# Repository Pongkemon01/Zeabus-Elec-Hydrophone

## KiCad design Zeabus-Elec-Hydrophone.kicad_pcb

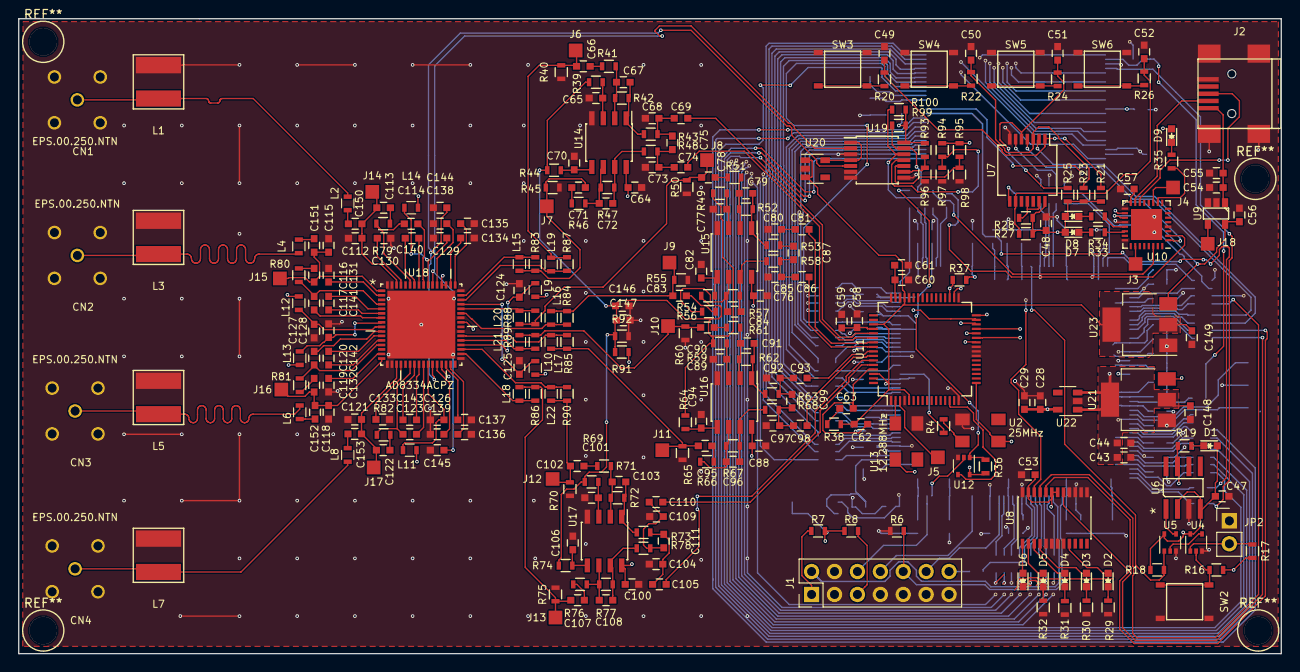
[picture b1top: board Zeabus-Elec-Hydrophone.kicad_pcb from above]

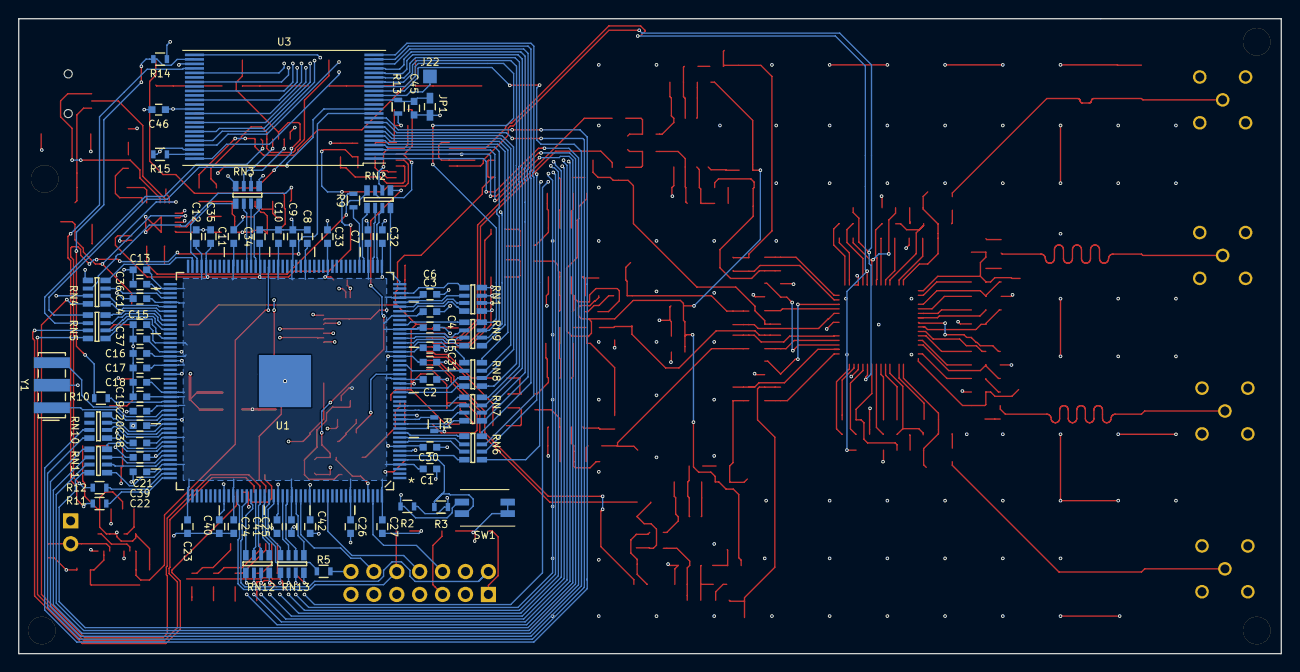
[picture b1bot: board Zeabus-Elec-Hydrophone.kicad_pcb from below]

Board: 4 copper layers, 140.0 x 70.4 mm, 352 parts (72 on the bottom side), 298 nets.

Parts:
C1, C2, C3, C4, C5, C6, C7, C8, C9, C10, C11, C12, C13, C14, C15, C16, C17, C18, C19, C20, C21, C22, C23, C24, C25, C26, C27, C30, C31, C32, C33, C34, C35, C36, C37, C38, C39, C40, C41, C42, C45, C46, C47, C48, C53, C55: 0.01uF; C_0603
C28, C29, C43, C44, C61, C146: 10uF; C_0603
C49, C50, C51, C52, C54, C56, C148, C149: 1uF; C_0603
C57, C58, C60, C64, C65, C70, C76, C77, C82, C88, C89, C94, C100, C101, C106, C114, C117, C120, C123, C124, C125, C126, C127, C128, C129, C130, C131, C132, C133, C134, C135, C136, C137, C138, C139, C140, C141, C142, C143, C150, C151, C152, C153: 0.1uF; C_0603
C59: 47uF; C_0603
C62: 390pF; C_0603
C63: 5600pF; C_0603
C66, C69, C71, C74, C78, C81, C83, C86, C90, C93, C95, C98, C102, C105, C107, C110: 22uF; C_0603
C67, C72, C79, C84, C91, C96, C103, C108: 300pF; C_0603
C68, C73, C80, C85, C92, C97, C104, C109, C144, C145: 1000pF; C_0603
C75, C87, C99, C111: 100pF; C_0603
C112, C115, C118, C121: 22pF; C_0603
C113, C116, C119, C122: 18000pF; C_0603
C147: 100uF; C_0603
CN1, CN2, CN3, CN4: EPS.00.250.NTN; EPS-00-250
D1, D2, D6: Yellow; LED_0603
D3, D8: Red; LED_0603
D4, D7: Blue; LED_0603
D5, D9: Green; LED_0603
J1: JTAG; Pin_Header_Straight_2x07_Pitch2.54mm
J2: USB_OTG; USB_Mini-B
J3, J4, J5, J6, J7, J8, J9, J10, J11, J12, J13, J14, J15, J16, J17, J18, J22: TEST_1P; 1Pin-TP
JP1: Write Protect; C_0603_HandSoldering
JP2: External Reset; Pin_Header_Straight_1x02_Pitch2.54mm
L1, L3, L5, L7: 15mH; L-SDR0503
L2, L4, L6, L8, L9, L10, L11, L12, L13, L14, L15, L16, L17, L18, L19, L20, L21, L22: 120nH; L_0603
R1, R2, R3, R7, R8, R13, R14, R15, R16, R17, R18, R21, R23, R25, R27, R28, R36, R37, R96, R97, R98, R99, R100: 10k; R_0603
R4, R5: 33; R_0603
R6: 47k; R_0603
R9, R10, R11, R12: 22; R_0603
R19, R29, R30, R31, R32, R33, R34, R35: 330; R_0603
R20, R22, R24, R26, R39, R44, R49, R54, R59, R64, R69, R74, R83, R84, R85, R86, R87, R88, R89, R90: 100; R_0603
R38: 560; R_0603
R40, R45, R50, R55, R60, R65, R70, R75: 49.9k; R_0603
R41, R46, R51, R56, R61, R66, R71, R76: 5.76k; R_0603
R42, R47, R52, R57, R62, R67, R72, R77: 4.99k; R_0603
R43, R48, R53, R58, R63, R68, R73, R78: 237; R_0603
R79, R80, R81, R82: 274; R_0603
R91: 806; R_0603
R92: 1k; R_0603
R93, R94, R95: 0; R_0603
RN1, RN2, RN3, RN4, RN5, RN6, RN7, RN8, RN9, RN10, RN11, RN12, RN13: EXBN8V-22; CRA06S
SW1: SW_DIP_x02; SW_DIP_x2_W5.08mm_Slide_Copal_CHS-A
SW2, SW3, SW4, SW5, SW6: PB; Button-EVQ
U1: ADSP-21489BSWZ-4B; ADSP-21489-177
U2: 25MHz; Oscillator-TCXO
U3: S29GL032N; TSOP-I-48_12x18.4mm_Pitch0.5mm
U4, U5, U12: 74LVC1G08; SOT-353
U6: ADM708SARZ; ADM708_R_8
U7: 74LVC14; SSOP-14_5.3x6.2mm_Pitch0.65mm
U8: 74AC11244; TSSOP-24_4.4x7.8mm_Pitch0.65mm
U9: NCP361SNT1G; TSOP-5
U10: FT232RQ; QFN-32-1EP_5x5mm_Pitch0.5mm
U11: AD1939WBSTZ; LQFP-64_10x10mm_Pitch0.5mm
U13: 12.288MHz; Oscillator-TCXO
U14, U15, U16, U17: AD8652ARZ; SOIC-8_3.9x4.9mm_Pitch1.27mm
U18: AD8334ACPZ; QFN50P900X900X100-65N
U19: MAX5387LAUD+T; TSSOP-14_4.4x5mm_Pitch0.65mm
U20: TLV73311PDBVT; SOT-23-5
U21, U23: LM1117-3.3; SOT-223-3Lead_TabPin2
U22: TLV73311PDVBT; SOT-23-5
Y1: CSTCC2M00G53-R0; Resonator_7.2x3mm

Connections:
+1V1: C1.1, C2.1, C3.1, C4.1, C5.1, C6.1, C7.1, C8.1, C9.1, C10.1, C11.1, C12.1, C13.1, C14.1, C15.1, C16.1, C17.1, C18.1, C19.1, C20.1, C21.1, C22.1, C23.1, C24.1, C25.1, C26.1, C27.1, C28.1, C29.1, U1.4, U1.23, U1.29, U1.34, U1.37, U1.41, U1.48, U1.62, U1.65, U1.68, U1.78, U1.85, U1.90, U1.93, U1.102, U1.105, U1.107, U1.113, U1.114, U1.116, U1.123, U1.129, U1.133, U1.143, U1.156, U1.169, U1.176, U22.5
+3.3VA: C62.1, C149.1, R38.2, U11.5, U11.45, U11.51, U11.62, U20.1, U20.3, U23.2
+3V3: C30.1, C31.1, C32.1, C33.1, C34.1, C35.1, C36.1, C37.1, C38.1, C39.1, C40.1, C41.1, C42.1, C43.1, C44.1, C46.1, C47.1, C48.1, C53.1, C148.1, D1.2, D7.2, D8.2, D9.2, R1.2, R7.2, R8.2, R13.1, R14.1, R16.1, R17.1, R18.1, R21.1, R23.1, R25.1, R27.1, R28.2, R36.1, R37.1, R93.1, R94.1, R95.1, R99.1, R100.1, SW1.1, SW1.2, U1.8, U1.28, U1.45, U1.57, U1.72, U1.84, U1.91, U1.104, U1.119, U1.126, U1.141, U1.153, U1.160, U2.VCC, U3.37, U4.5, U5.5, U6.2, U6.4, U7.14, U8.18, U8.19, U8.23, U11.17, U11.32, U12.5, U13.VCC, U19.14, U21.2, U22.1, U22.3
+5V: C56.1, C64.2, C76.2, C88.2, C100.2, L9.1, L10.1, L11.1, L12.1, L13.1, L14.1, R91.1, U9.5, U10.19, U14.8, U15.8, U16.8, U17.8, U18.29, U18.41, U18.51, U18.52, U21.3, U23.3
/ADC/ABCLK: RN3.1, U11.28
/ADC/ADC1LN: C74.2, U11.54
/ADC/ADC1LP: C69.2, U11.53
/ADC/ADC1RN: C86.2, U11.56
/ADC/ADC1RP: C81.2, U11.55
/ADC/ADC2LN: C98.2, U11.58
/ADC/ADC2LP: C93.2, U11.57
/ADC/ADC2RN: C110.2, U11.60
/ADC/ADC2RP: C105.2, U11.59
/ADC/ALRCLK: RN4.3, U11.29
/ADC/ASDATA1: RN4.1, U11.27
/ADC/ASDATA2: RN3.4, U11.26
/ADC/SPI_CLK: RN1.3, U11.34
/ADC/SPI_MISO: RN1.1, U11.31
/ADC/~AD1939_CS: R37.2, RN1.4, U11.35
/ADC/~AD1939_SOFT_RESET: R36.2, RN2.1, U12.1
/DSP-External_Port/DAI_P5_Z: RN4.8, U1.87
/DSP-External_Port/DAI_P6_Z: RN3.5, U1.86
/DSP-External_Port/DAI_P7_Z: RN3.8, U1.73
/DSP-External_Port/DAI_P8_Z: RN4.6, U1.94
/DSP-External_Port/DAI_P13_Z: RN3.7, U1.74
/DSP-External_Port/DAI_P14_Z: RN4.5, U1.95
/DSP-External_Port/DAI_P15_Z: RN5.5, U1.101
/DSP-External_Port/DAI_P16_Z: RN5.6, U1.99
/DSP-External_Port/DAI_P17_Z: RN5.7, U1.98
/DSP-External_Port/DAI_P18_Z: RN5.8, U1.97
/DSP-External_Port/DAI_P19_Z: RN3.6, U1.75
/DSP-External_Port/DAI_P20_Z: RN4.7, U1.92
/DSP-External_Port/DPI_P1_Z: RN1.8, U1.38
/DSP-External_Port/DPI_P2_Z: RN1.7, U1.39
/DSP-External_Port/DPI_P3_Z: RN1.6, U1.40
/DSP-External_Port/DPI_P5_Z: RN1.5, U1.42
/DSP-External_Port/DPI_P6_Z: RN2.8, U1.44
/DSP-External_Port/DPI_P7_Z: RN2.6, U1.47
/DSP-External_Port/DPI_P8_Z: RN2.7, U1.46
/DSP-External_Port/DPI_P9_Z: RN2.5, U1.49
/DSP-External_Port/DPI_P10_Z: R9.2, U1.50
/DSP-External_Port/LED1: RN3.2, U8.22
/DSP-External_Port/LED2: RN4.4, U8.21
/DSP-External_Port/LED3: RN5.4, U8.20
/DSP-External_Port/LED4: RN5.3, U8.17
/DSP-External_Port/PB1: RN5.2, U7.2
/DSP-External_Port/PB2: RN5.1, U7.4
/DSP-External_Port/PB3: RN3.3, U7.6
/DSP-External_Port/PB4: RN4.2, U7.8
/DSP-External_Port/SCL: R99.2, RN2.2, U19.13
/DSP-External_Port/SDA: R100.2, RN2.3, U19.12
/DSP-External_Port/SPI_MISO: RN1.2, U11.30
/DSP-External_Port/UART_RX: R9.1, U10.2
/DSP-External_Port/UART_TX: RN2.4, U10.30
/DSP-Memory/A0: RN6.1, U3.45
/DSP-Memory/A0_Z: RN6.8, U1.6
/DSP-Memory/A1: RN6.2, U3.25
/DSP-Memory/A1_Z: RN6.7, U1.9
/DSP-Memory/A2: RN6.3, U3.24
/DSP-Memory/A2_Z: RN6.6, U1.10
/DSP-Memory/A3: RN6.4, U3.23
/DSP-Memory/A3_Z: RN6.5, U1.11
/DSP-Memory/A4: RN7.1, U3.22
/DSP-Memory/A4_Z: RN7.8, U1.12
/DSP-Memory/A5: RN7.2, U3.21
/DSP-Memory/A5_Z: RN7.7, U1.13
/DSP-Memory/A6: RN7.3, U3.20
/DSP-Memory/A6_Z: RN7.6, U1.16
/DSP-Memory/A7: RN7.4, U3.19
/DSP-Memory/A7_Z: RN7.5, U1.17
/DSP-Memory/A8: RN8.1, U3.18
/DSP-Memory/A8_Z: RN8.8, U1.20
/DSP-Memory/A9: RN8.2, U3.8
/DSP-Memory/A9_Z: RN8.7, U1.21
/DSP-Memory/A10: RN8.3, U3.7
/DSP-Memory/A10_Z: RN8.6, U1.26
/DSP-Memory/A11: RN8.4, U3.6
/DSP-Memory/A11_Z: RN8.5, U1.30
/DSP-Memory/A12: RN9.1, U3.5
/DSP-Memory/A12_Z: RN9.8, U1.31
/DSP-Memory/A13: RN9.3, U3.4
/DSP-Memory/A13_Z: RN9.6, U1.33
/DSP-Memory/A14: RN11.4, U3.3
/DSP-Memory/A14_Z: RN11.5, U1.130
/DSP-Memory/A15: RN11.3, U3.2
/DSP-Memory/A15_Z: RN11.6, U1.128
/DSP-Memory/A16: RN11.2, U3.1
/DSP-Memory/A16_Z: RN11.7, U1.127
/DSP-Memory/A17: RN9.2, U3.48
/DSP-Memory/A17_Z: RN9.7, U1.32
/DSP-Memory/A18: RN9.4, U3.17
/DSP-Memory/A18_Z: RN9.5, U1.35
/DSP-Memory/A19: RN11.1, U3.16
/DSP-Memory/A19_Z: RN11.8, U1.125
/DSP-Memory/A20: RN10.4, U3.9
/DSP-Memory/A20_Z: RN10.5, U1.124
/DSP-Memory/A21: RN10.3, U3.10
/DSP-Memory/A21_Z: RN10.6, U1.122
/DSP-Memory/A22_Z: RN10.7, U1.121
/DSP-Memory/A23_Z: RN10.8, U1.120
/DSP-Memory/D0: RN12.1, U3.29
/DSP-Memory/D0_Z: RN12.8, U1.147
/DSP-Memory/D1: RN12.2, U3.31
/DSP-Memory/D1_Z: RN12.7, U1.148
/DSP-Memory/D2: RN12.3, U3.33
/DSP-Memory/D2_Z: RN12.6, U1.149
/DSP-Memory/D3: RN12.4, U3.35
/DSP-Memory/D3_Z: RN12.5, U1.150
/DSP-Memory/D4: RN13.1, U3.38
/DSP-Memory/D4_Z: RN13.8, U1.152
/DSP-Memory/D5: RN13.2, U3.40
/DSP-Memory/D5_Z: RN13.7, U1.154
/DSP-Memory/D6: RN13.3, U3.42
/DSP-Memory/D6_Z: RN13.6, U1.155
/DSP-Memory/D7: RN13.4, U3.44
/DSP-Memory/D7_Z: RN13.5, U1.157
/DSP-Memory/~AMI_RD: R11.1, U1.132
/DSP-Memory/~AMI_WR: R12.1, U1.131
/DSP-Memory/~Flash_CS: R10.2, R14.2, U3.26
/DSP-Memory/~MS1: R10.1, U1.115
/DSP-Memory/~RD: R11.2, U3.28
/DSP-Memory/~WR: R12.2, U3.11
/DSP_Misc/D+: J2.3, U10.14
/DSP_Misc/D-: J2.2, U10.15
/LNA/GAIN12: C145.1, U18.54, U19.2
/LNA/GAIN34: C144.1, U18.27, U19.5
/LNA/IN1: CN1.1, L1.1, L2.1
/LNA/IN2: CN2.1, L3.1, L4.1
/LNA/IN3: CN3.1, L5.1, L6.1
/LNA/IN4: CN4.1, L7.1, L8.1
/LNA/INH1: C112.1, C113.1, C150.2, J14.1, U18.62
/LNA/INH2: C115.1, C116.1, C151.2, J15.1, U18.1
/LNA/INH3: C118.1, C119.1, C152.2, J16.1, U18.16
/LNA/INH4: C121.1, C122.1, C153.2, J17.1, U18.19
/LNA/LNA1LN: C66.2, J6.1, L19.2, R40.2, R87.2
/LNA/LNA1LP: C71.2, J7.1, L15.2, R45.2, R83.2
/LNA/LNA1RN: C78.2, J8.1, L20.2, R50.2, R88.2
/LNA/LNA1RP: C83.2, J9.1, L16.2, R55.2, R84.2
/LNA/LNA2LN: C90.2, J10.1, L21.2, R60.2, R89.2
/LNA/LNA2LP: C95.2, J11.1, L17.2, R65.2, R85.2
/LNA/LNA2RN: C102.2, J12.1, L22.2, R70.2, R90.2
/LNA/LNA2RP: C107.2, J13.1, L18.2, R75.2, R86.2
/LNA/LON1: C114.1, R79.2, U18.59
/LNA/LON2: C117.1, R80.2, U18.4
/LNA/LON3: C120.1, R81.2, U18.13
/LNA/LON4: C123.1, R82.2, U18.22
/LNA/LOP1: C140.1, U18.58
/LNA/LOP2: C141.1, U18.5
/LNA/LOP3: C142.1, U18.12
/LNA/LOP4: C143.1, U18.23
/LNA/VIN1: C114.2, U18.56
/LNA/VIN2: C117.2, U18.7
/LNA/VIN3: C120.2, U18.10
/LNA/VIN4: C123.2, U18.25
/LNA/VIP1: C140.2, U18.57
/LNA/VIP2: C141.2, U18.6
/LNA/VIP3: C142.2, U18.11
/LNA/VIP4: C143.2, U18.24
GND: C1.2, C2.2, C3.2, C4.2, C5.2, C6.2, C7.2, C8.2, C9.2, C10.2, C11.2, C12.2, C13.2, C14.2, C15.2, C16.2, C17.2, C18.2, C19.2, C20.2, C21.2, C22.2, C23.2, C24.2, C25.2, C26.2, C27.2, C28.2, C29.2, C30.2, C31.2, C32.2, C33.2, C34.2, C35.2, C36.2, C37.2, C38.2, C39.2, C40.2, C41.2, C42.2, C43.2, C44.2, C45.2, C46.2, C47.2, C48.2, C49.2, C50.2, C51.2, C52.2, C53.2, C54.2, C55.2, C56.2, C57.1, C58.2, C59.2, C60.2, C61.2, C64.1, C65.2, C68.1, C70.2, C73.1, C76.1, C77.2, C80.1, C82.2, C85.1, C88.1, C89.2, C92.1, C94.2, C97.1, C100.1, C101.2, C104.1, C106.2, C109.1, C112.2, C115.2, C118.2, C121.2, C124.2, C125.2, C126.2, C127.2, C128.2, C129.2, C130.1, C131.1, C132.1, C133.1, C134.1, C135.1, C136.1, C137.1, C138.1, C139.1, C144.2, C145.2, C146.2, C147.2, C148.2, C149.2, CN1.2, CN1.3, CN1.4, CN1.5, CN2.2, CN2.3, CN2.4, CN2.5, CN3.2, CN3.3, CN3.4, CN3.5, CN4.2, CN4.3, CN4.4, CN4.5, J1.3, J1.4, J1.7, J1.9, J1.11, J1.13, J2.5, J2.6, JP1.2, JP2.1, L1.2, L3.2, L5.2, L7.2, R2.1, R3.1, R6.1, R15.2, R29.1, R30.1, R31.1, R32.1, R40.1, R45.1, R50.1, R55.1, R60.1, R65.1, R70.1, R75.1, R92.2, R96.2, R97.2, R98.2, SW2.1, SW2.3, SW3.1, SW3.3, SW4.1, SW4.3, SW5.1, SW5.3, SW6.1, SW6.3, U1.7, U1.15, U1.106, U1.109, U1.177, U2.GND, U3.27, U3.46, U4.3, U5.3, U6.3, U7.7, U8.5, U8.6, U8.7, U8.8, U8.13, U8.14, U8.15, U8.16, U8.24, U9.2, U9.3, U10.4, U10.17, U10.20, U10.24, U11.1, U11.4, U11.16, U11.23, U11.24, U11.25, U11.33, U11.44, U11.46, U11.48, U12.3, U13.GND, U14.4, U15.4, U16.4, U17.4, U18.17, U18.18, U18.33, U18.39, U18.42, U18.48, U18.63, U18.64, U18.65, U19.3, U19.6, U19.7, U19.8, U20.2, U21.1, U22.2, U23.1, Y1.2
unnamed: C45.1, JP1.1, R13.2, U3.14
unnamed: C49.1, R20.1, R21.2, U7.1
unnamed: C50.1, R22.1, R23.2, U7.3
unnamed: C51.1, R24.1, R25.2, U7.5
unnamed: C52.1, R26.1, R27.2, U7.9
unnamed: C54.1, C55.1, J2.1, U9.1
unnamed: C57.2, U10.1, U10.16
unnamed: C58.1, C59.1, U11.52
unnamed: C60.1, C61.1, U11.47
unnamed: C62.2, C63.2, U11.61
unnamed: C63.1, R38.1
unnamed: C65.1, R39.1, U14.3
unnamed: C66.1, R41.2
unnamed: C67.1, R42.1, R43.2, U14.1
unnamed: C67.2, R41.1, R42.2, U14.2
unnamed: C68.2, C69.1, C75.2, R43.1
unnamed: C70.1, R44.1, U14.5
unnamed: C71.1, R46.2
unnamed: C72.1, R47.1, R48.2, U14.7
unnamed: C72.2, R46.1, R47.2, U14.6
unnamed: C73.2, C74.1, C75.1, R48.1
unnamed: C77.1, R49.1, U15.3
unnamed: C78.1, R51.2
unnamed: C79.1, R52.1, R53.2, U15.1
unnamed: C79.2, R51.1, R52.2, U15.2
unnamed: C80.2, C81.1, C87.2, R53.1
unnamed: C82.1, R54.1, U15.5
unnamed: C83.1, R56.2
unnamed: C84.1, R57.1, R58.2, U15.7
unnamed: C84.2, R56.1, R57.2, U15.6
unnamed: C85.2, C86.1, C87.1, R58.1
unnamed: C89.1, R59.1, U16.3
unnamed: C90.1, R61.2
unnamed: C91.1, R62.1, R63.2, U16.1
unnamed: C91.2, R61.1, R62.2, U16.2
unnamed: C92.2, C93.1, C99.2, R63.1
unnamed: C94.1, R64.1, U16.5
unnamed: C95.1, R66.2
unnamed: C96.1, R67.1, R68.2, U16.7
unnamed: C96.2, R66.1, R67.2, U16.6
unnamed: C97.2, C98.1, C99.1, R68.1
unnamed: C101.1, R69.1, U17.3
unnamed: C102.1, R71.2
unnamed: C103.1, R72.1, R73.2, U17.1
unnamed: C103.2, R71.1, R72.2, U17.2
unnamed: C104.2, C105.1, C111.2, R73.1
unnamed: C106.1, R74.1, U17.5
unnamed: C107.1, R76.2
unnamed: C108.1, R77.1, R78.2, U17.7
unnamed: C108.2, R76.1, R77.2, U17.6
unnamed: C109.2, C110.1, C111.1, R78.1
unnamed: C113.2, R79.1
unnamed: C116.2, R80.1
unnamed: C119.2, R81.1
unnamed: C122.2, R82.1
unnamed: C124.1, L9.2, U18.36
unnamed: C125.1, L10.2, U18.45
unnamed: C126.1, L11.2, U18.26
unnamed: C127.1, L12.2, U18.9
unnamed: C128.1, L13.2, U18.8
unnamed: C129.1, L14.2, U18.55
unnamed: C130.2, U18.61
unnamed: C131.2, U18.2
unnamed: C132.2, U18.15
unnamed: C133.2, U18.20
unnamed: C134.2, U18.50
unnamed: C135.2, U18.49
unnamed: C136.2, U18.31
unnamed: C137.2, U18.30
unnamed: C138.2, U18.53
unnamed: C139.2, U18.28
unnamed: C150.1, L2.2
unnamed: C151.1, L4.2
unnamed: C152.1, L6.2
unnamed: C153.1, L8.2
unnamed: D1.1, R19.1
unnamed: D2.1, R29.2
unnamed: D2.2, U8.9
unnamed: D3.1, R30.2
unnamed: D3.2, U8.4
unnamed: D4.1, R31.2
unnamed: D4.2, U8.3
unnamed: D5.1, D6.1, R32.2
unnamed: D5.2, U8.2
unnamed: D6.2, U8.1
unnamed: D7.1, R33.2
unnamed: D8.1, R34.2
unnamed: D9.1, R35.2
unnamed: J1.1, R7.1
unnamed: J1.2, U1.146
unnamed: J1.5, R8.1
unnamed: J1.6, U1.174
unnamed: J1.8, U1.164
unnamed: J1.10, R6.2, U1.144
unnamed: J1.12, U1.158
unnamed: J1.14, R5.2
unnamed: J3.1, U10.26
unnamed: J4.1, U10.11
unnamed: J5.1, U11.3
unnamed: J18.1, U9.4
unnamed: J22.1, U3.15
unnamed: JP2.2, R17.2, U4.1
unnamed: L15.1, R83.1, U18.47
unnamed: L16.1, R84.1, U18.43
unnamed: L17.1, R85.1, U18.38
unnamed: L18.1, R86.1, U18.34
unnamed: L19.1, R87.1, U18.46
unnamed: L20.1, R88.1, U18.44
unnamed: L21.1, R89.1, U18.37
unnamed: L22.1, R90.1, U18.35
unnamed: R1.1, U1.14
unnamed: R2.2, SW1.3, U1.22
unnamed: R3.2, SW1.4, U1.5
unnamed: R4.1, U2.OUT
unnamed: R4.2, U1.24
unnamed: R5.1, U1.151
unnamed: R15.1, U3.47
unnamed: R16.2, SW2.2, SW2.4, U4.2
unnamed: R18.2, U1.70, U5.1
unnamed: R20.2, SW3.2, SW3.4
unnamed: R22.2, SW4.2, SW4.4
unnamed: R24.2, SW5.2, SW5.4
unnamed: R26.2, SW6.2, SW6.4
unnamed: R28.1, U7.11, U7.13
unnamed: R33.1, U10.22
unnamed: R34.1, U10.21
unnamed: R35.1, U10.10
unnamed: R93.2, R96.1, U19.9
unnamed: R94.2, R97.1, U19.11
unnamed: R95.2, R98.1, U19.10
unnamed: U1.117, Y1.3
unnamed: U1.118, Y1.1
unnamed: U4.4, U5.2
unnamed: U5.4, U6.1
unnamed: U11.2, U13.OUT
unnamed: U11.14, U12.4
unnamed: U19.1, U19.4, U20.5
VA_REF: C146.1, C147.1, R39.2, R44.2, R49.2, R54.2, R59.2, R64.2, R69.2, R74.2, R91.2, R92.1
~RESET: R19.2, U1.173, U3.12, U6.7, U10.18, U12.2

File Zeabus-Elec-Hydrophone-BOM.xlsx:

Reference | Quantity | Value | Footprint | Element14 Code
C113 C116 C119 C122 | 4 | 18000pF | Capacitors_SMD:C_0603_HandSoldering | MC0603B183K
C1 C10 C11 C12 C13 C14 C15 C16 C17 C18 C19 C2 C20 C21 C22 C23 C24 C25 C26 C27 C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 | 46 | 0.01uF | Capacitors_SMD:C_0603_HandSoldering | C0603C103M3
C147 | 1 | 100uF | Capacitors_SMD:C_0603_HandSoldering | GRM31CF50J107
C148 C149 C49 C50 C51 C52 C54 C56 | 8 | 1uF | Capacitors_SMD:C_0603_HandSoldering | MC0603X105K
C146 C28 C29 C43 C44 C61 | 6 | 10uF | Capacitors_SMD:C_0603_HandSoldering | GRM188R60J106
C100 C101 C106 C112 C114 C115 C117 C118 C120 C121 C123 C124 C125 C126 C127 C128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 | 43 | 0.1uF | Capacitors_SMD:C_0603_HandSoldering | MC0603B104J
C59 | 1 | 47uF | Capacitors_SMD:C_1206_HandSoldering | GRT31CR60J476
C62 | 1 | 390pF | Capacitors_SMD:C_0603_HandSoldering | C0603C391F5
C63 | 1 | 5600pF | Capacitors_SMD:C_0603_HandSoldering | 06031C562JA
C102 C105 C107 C110 C66 C69 C71 C74 C78 C81 C83 C86 C90 C93 C95 C98 | 16 | 22uF | Capacitors_SMD:C_0805_HandSoldering | JMK212BJ226
C103 C108 C67 C72 C79 C84 C91 C96 | 8 | 300pF | Capacitors_SMD:C_0603_HandSoldering | C0603C301J5
C104 C109 C144 C145 C68 C73 C80 C85 C92 C97 | 10 | 1000pF | Capacitors_SMD:C_0603_HandSoldering | MCMT18N102
C111 C75 C87 C99 | 4 | 100pF | Capacitors_SMD:C_0603_HandSoldering | MCMT18N101
CN1 CN2 CN3 CN4 | 4 | EPS.00.250.NTN | Zeabus:EPS-00-250 | EPS.00.250.NTN (DigiKey)
D1 D2 D6 | 3 | Yellow | LEDs:LED_0603 | MCL-S290YC
D3 D8 | 2 | Red | LEDs:LED_0603 | MCL-S290SRC
D4 D7 | 2 | Blue | LEDs:LED_0603 | MCL-S291SBLC
D5 D9 | 2 | Green | LEDs:LED_0603 | SML-LX0603GW
J1 | 1 | JTAG | Pin_Headers:Pin_Header_Straight_2x07_Pitch2.54mm | N2514-6002RB
J2 | 1 | USB_OTG | Connectors:USB_Mini-B | UX60SC-MB-5ST(80)
J10 J11 J12 J13 J14 J15 J16 J17 J18 J22 J3 J4 J5 J6 J7 J8 J9 | 17 | TEST_1P | SMD_Packages:1Pin | (Empty)
JP1 | 1 | Write Protect | Capacitors_SMD:C_0603_HandSoldering | (Empty)
JP2 | 1 | External Reset | Pin_Headers:Pin_Header_Straight_1x02_Pitch2.54mm | (Empty)
L1 L3 L5 L7 | 4 | 15mH | Zeabus:L-SDR0503 | SDR0503-153JL
L10 L11 L12 L13 L14 L15 L16 L17 L18 L19 L2 L20 L21 L4 L6 L8 L9 L22 | 18 | 120nH | Inductors_SMD:L_0603_HandSoldering | ELJRER12GFA
R1 R13 R14 R15 R16 R17 R18 R2 R21 R23 R25 R27 R28 R3 R36 R37 R7 R8 R96 R97 R98 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 | 23 | 10k | Resistors_SMD:R_0603_HandSoldering
R19 R29 R30 R31 R32 R33 R34 R35 | 8 | 330 | Resistors_SMD:R_0603_HandSoldering
R20 R22 R24 R26 R39 R44 R49 R54 R59 R64 R69 R74 R83 R84 R85 R86 R87 R88 R89 R90 | 20 | 100 | Resistors_SMD:R_0603_HandSoldering
R38 | 1 | 560 | Resistors_SMD:R_0603_HandSoldering
R4 R5 | 2 | 33 | Resistors_SMD:R_0603_HandSoldering
R40 R45 R50 R55 R60 R65 R70 R75 | 8 | 49.9k | Resistors_SMD:R_0603_HandSoldering
R41 R46 R51 R56 R61 R66 R71 R76 | 8 | 5.76k | Resistors_SMD:R_0603_HandSoldering
R42 R47 R52 R57 R62 R67 R72 R77 | 8 | 4.99k | Resistors_SMD:R_0603_HandSoldering
R43 R48 R53 R58 R63 R68 R73 R78 | 8 | 237 | Resistors_SMD:R_0603_HandSoldering
R6 | 1 | 47k | Resistors_SMD:R_0603_HandSoldering
R79 R80 R81 R82 | 4 | 274 | Resistors_SMD:R_0603_HandSoldering
R10 R11 R12 R9 | 4 | 22 | Resistors_SMD:R_0603_HandSoldering
R91 | 1 | 806 | Resistors_SMD:R_0603_HandSoldering
R92 | 1 | 1k | Resistors_SMD:R_0603_HandSoldering
R93 R94 R95 | 3 | 0 | Resistors_SMD:R_0603_HandSoldering | (Empty)
RN1 RN10 RN11 RN12 RN13 RN2 RN3 RN4 RN5 RN6 RN7 RN8 RN9 | 13 | EXBN8V-22 | Zeabus:CRA06S | CRA06S08322R0
SW1 | 1 | SW_DIP_x02 | Buttons_Switches_SMD:SW_DIP_x2_W5.08mm_Slide_Copal_CHS-A | MCDM(R)-02-T
SW2 SW3 SW4 SW5 SW6 | 5 | PB | Zeabus:Button-EVQ | EVQPT5A15
U1 | 1 | ADSP-21489BSWZ-4B | Zeabus:ADSP-21489-177 | ADSP-21489BSWZ-4B
U10 | 1 | FT232RQ | Housings_DFN_QFN:QFN-32-1EP_5x5mm_Pitch0.5mm | FT232RQ
U11 | 1 | AD1939WBSTZ | Housings_QFP:LQFP-64_10x10mm_Pitch0.5mm | AD1939WBSTZ
U13 | 1 | FOX924B - 12.288MHz | Zeabus:Oscillator-TCXO | FOX924B - 12.288MHz
U14 U15 U16 U17 | 4 | AD8652ARZ | Housings_SOIC:SOIC-8_3.9x4.9mm_Pitch1.27mm | AD8652ARZ
U18 | 1 | AD8334ACPZ | Zeabus:QFN50P900X900X100-65N | AD8334ACPZ
U19 | 1 | MAX5387LAUD+T | Housings_SSOP:TSSOP-14_4.4x5mm_Pitch0.65mm | MAX5387LAUD+T
U2 | 1 | FOX924B - 25MHz | Zeabus:Oscillator-TCXO | FOX924B - 25MHz
U20 | 1 | TLV73311PDBVT | TO_SOT_Packages_SMD:SOT-23-5_HandSoldering | TLV73311PDBVT
U21 U23 | 2 | LM1117-3.3 | TO_SOT_Packages_SMD:SOT-223-3Lead_TabPin2 | LM1117-3.3
U22 | 1 | TLV73311PDVBT | TO_SOT_Packages_SMD:SOT-23-5_HandSoldering | TLV73311PDVBT
U3 | 1 | S29GL032N | Housings_SSOP:TSOP-I-48_12x18.4mm_Pitch0.5mm | S29GL032N90TFI40
U12 U4 U5 | 3 | 74LVC1G08 | TO_SOT_Packages_SMD:SOT-353 | 74LVC1G08GW
U6 | 1 | ADM708SARZ | Zeabus:ADM708_R_8 | ADM708SARZ
U7 | 1 | 74LVC14 | Housings_SSOP:SSOP-14_5.3x6.2mm_Pitch0.65mm | 74LVC14APW
U8 | 1 | 74AC11244 | Housings_SSOP:TSSOP-24_4.4x7.8mm_Pitch0.65mm | 74AC11244APW
U9 | 1 | NCP361SNT1G | Zeabus:TSOP-5 | NCP361SNT1G
Y1 | 1 | CSTCC2M00G53-R0 | Crystals:Resonator_7.2x3mm | CSTCC2M00G53-R0

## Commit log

2017-08-22 First release of the schematic.
2017-08-23 First schematic release
2017-09-01 - Add C150 - C153 at LNA input - Change value of C112, C115, C118, C221 at LNA input - Finished PCB lay-out. Ready to route
2017-09-12 Finished PCB routing. Ready for manufacture
2017-09-17 Add stitched vias around analog components
2017-10-20 Correction for silkscreen and add board-holding knot-hole
2017-11-07 Bug fixed of misplaced via
